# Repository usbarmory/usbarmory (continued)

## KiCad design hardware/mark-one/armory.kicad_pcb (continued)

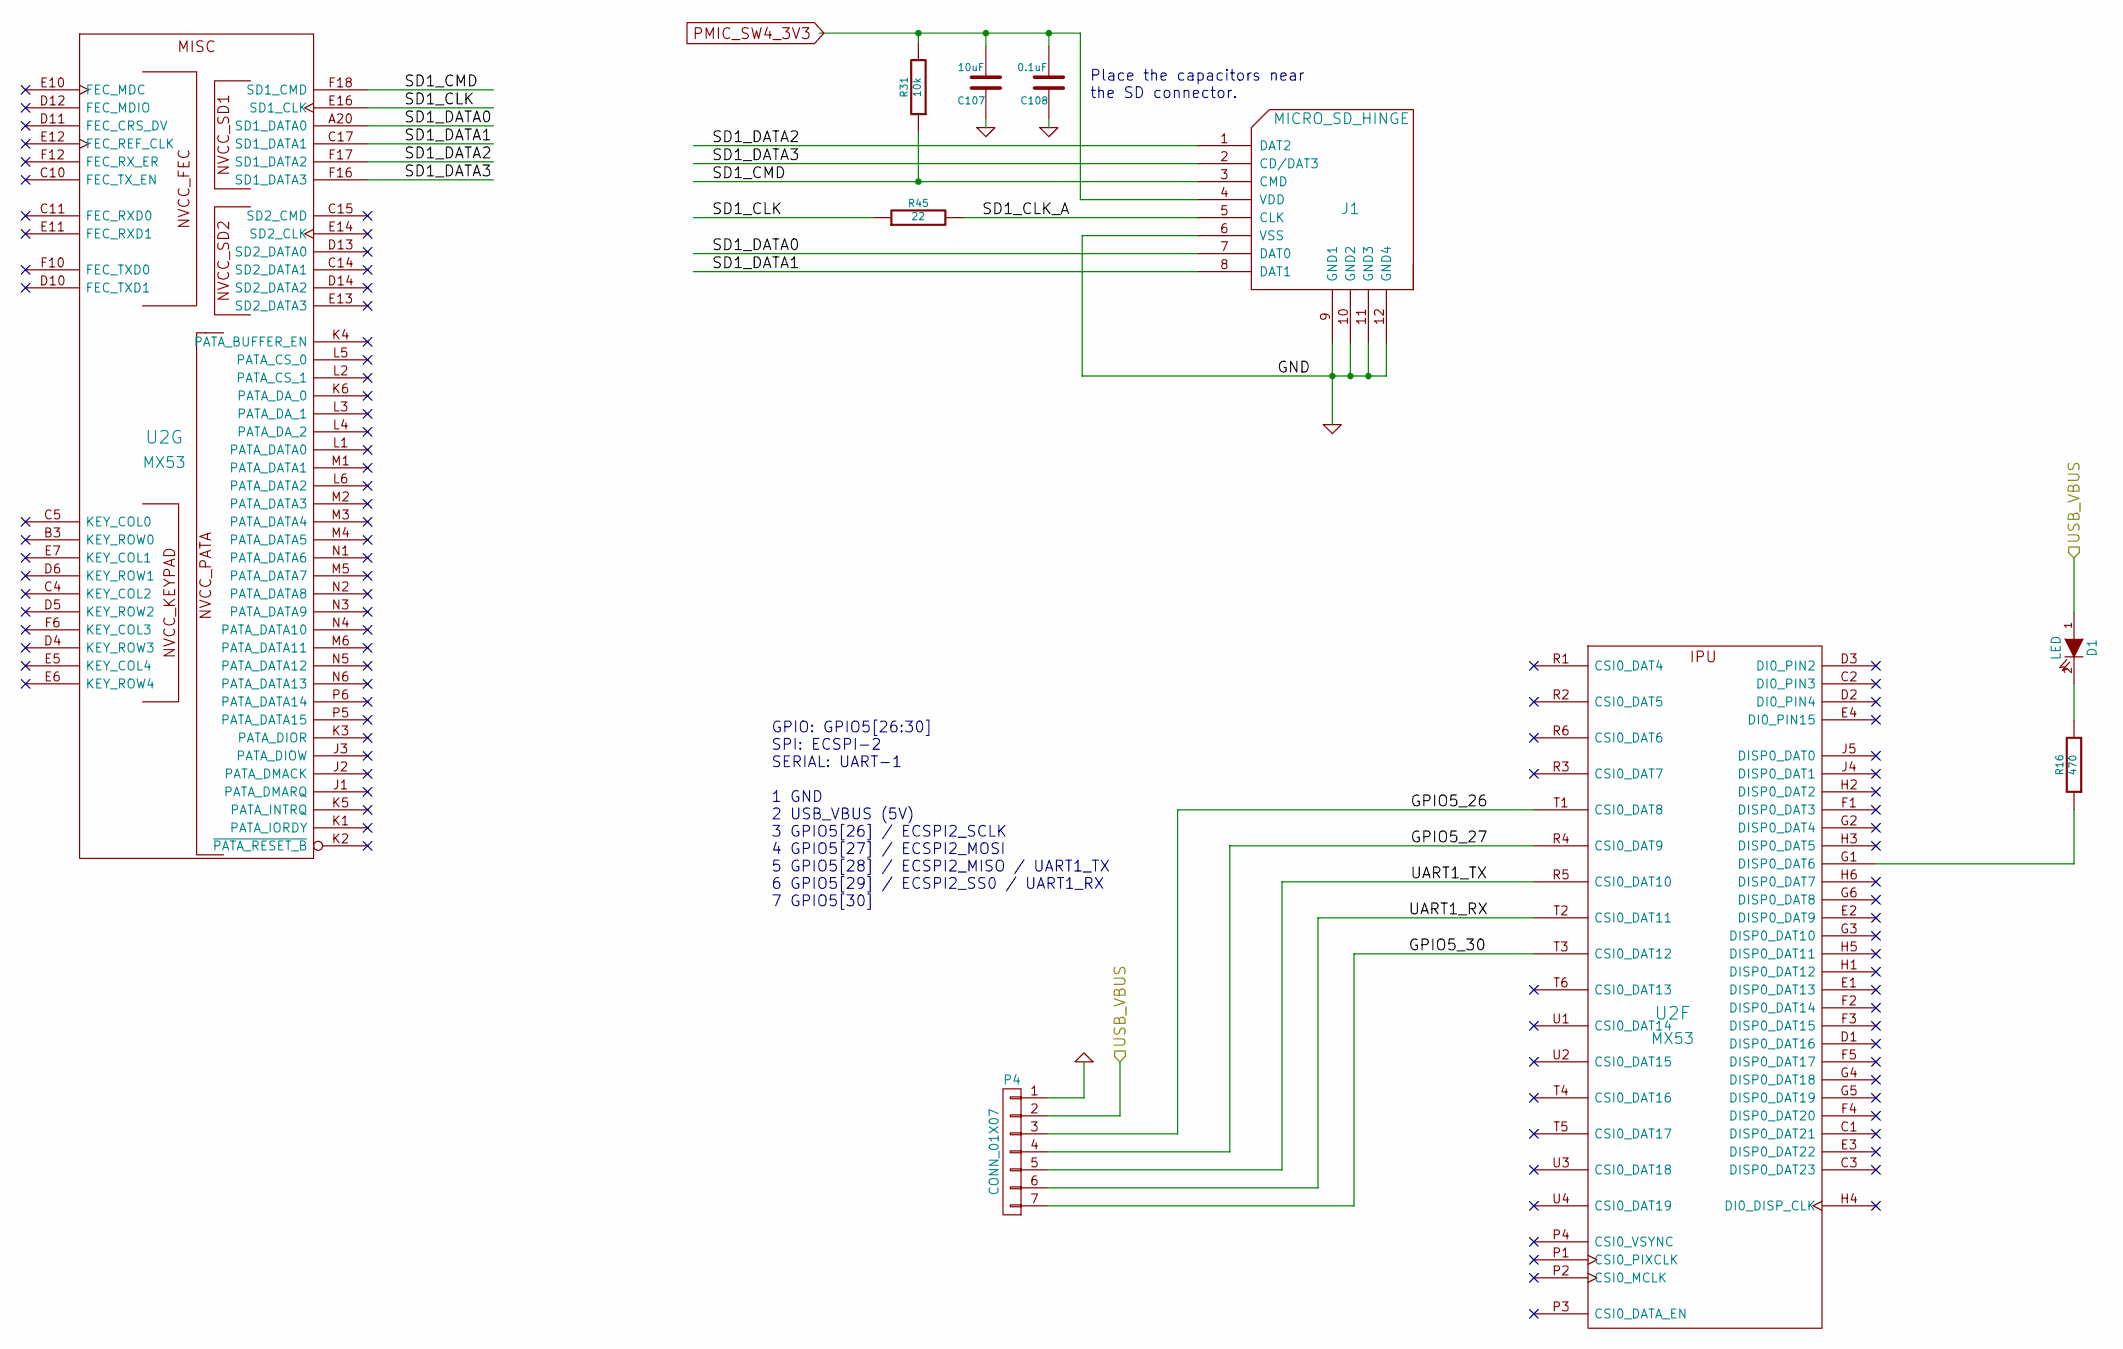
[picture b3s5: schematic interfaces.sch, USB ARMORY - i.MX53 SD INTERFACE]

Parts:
C107: 10uF; SM0603; Mfg PN C1608X5R1A106K080AC
C108: 0.1uF; SM0201; Mfg PN C0603X5R0J104K030BC
D1: LED; SM0603LED; Mfg PN VLMW1300-GS08
J1: MICRO_SD_HINGE; MICRO_SD_HINGE_AMP; Mfg PN 101-00303-68
P4: CONN_01X07; pinhead-1X7
R16: 470; SM0201; Mfg PN CRCW0201470RFNED
R31: 10k; SM0201; Mfg PN CRCW020110K0FNED
R45: 22; SM0201; Mfg PN CRCW020122R0FNED
U2: MX53

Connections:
/Interfaces/GPIO5_26: P4.3, U2.T1 (CSI0_DAT8)
/Interfaces/GPIO5_27: P4.4, U2.R4 (CSI0_DAT9)
/Interfaces/GPIO5_30: P4.7, U2.T3 (CSI0_DAT12)
/Interfaces/SD1_CLK: R45.1, U2.E16 (SD1_CLK)
/Interfaces/SD1_CLK_A: J1.5 (CLK), R45.2
/Interfaces/SD1_CMD: J1.3 (CMD), R31.1, U2.F18 (SD1_CMD)
/Interfaces/SD1_DATA0: J1.7 (DAT0), U2.A20 (SD1_DATA0)
/Interfaces/SD1_DATA1: J1.8 (DAT1), U2.C17 (SD1_DATA1)
/Interfaces/SD1_DATA2: J1.1 (DAT2), U2.F17 (SD1_DATA2)
/Interfaces/SD1_DATA3: J1.2 (CD/DAT3), U2.F16 (SD1_DATA3)
/Interfaces/UART1_RX: P4.6, U2.T2 (CSI0_DAT11)
/Interfaces/UART1_TX: P4.5, U2.R5 (CSI0_DAT10)
/Interfaces/USB_VBUS: D1.1 (A), P4.2; also elsewhere on the board
GND: C107.1, C108.1, J1.6 (VSS), J1.9 (GND1), J1.10 (GND2), J1.11 (GND3), J1.12 (GND4), P4.1; also elsewhere on the board
unnamed: D1.2 (K), R16.2
unnamed: R16.1, U2.G1 (DISP0_DAT6)
PMIC_SW4_3V3: C107.2, C108.2, J1.4 (VDD), R31.2; also elsewhere on the board

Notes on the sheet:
Place the capacitors near the SD connector.
GPIO: GPIO5[26:30] SPI: ECSPI-2 SERIAL: UART-1 1 GND 2 USB_VBUS (5V) 3 GPIO5[26] / ECSPI2_SCLK 4 GPIO5[27] / ECSPI2_MOSI 5 GPIO5[28] / ECSPI2_MISO / UART1_TX 6 GPIO5[29] / ECSPI2_SS0 / UART1_RX 7 GPIO5[30]

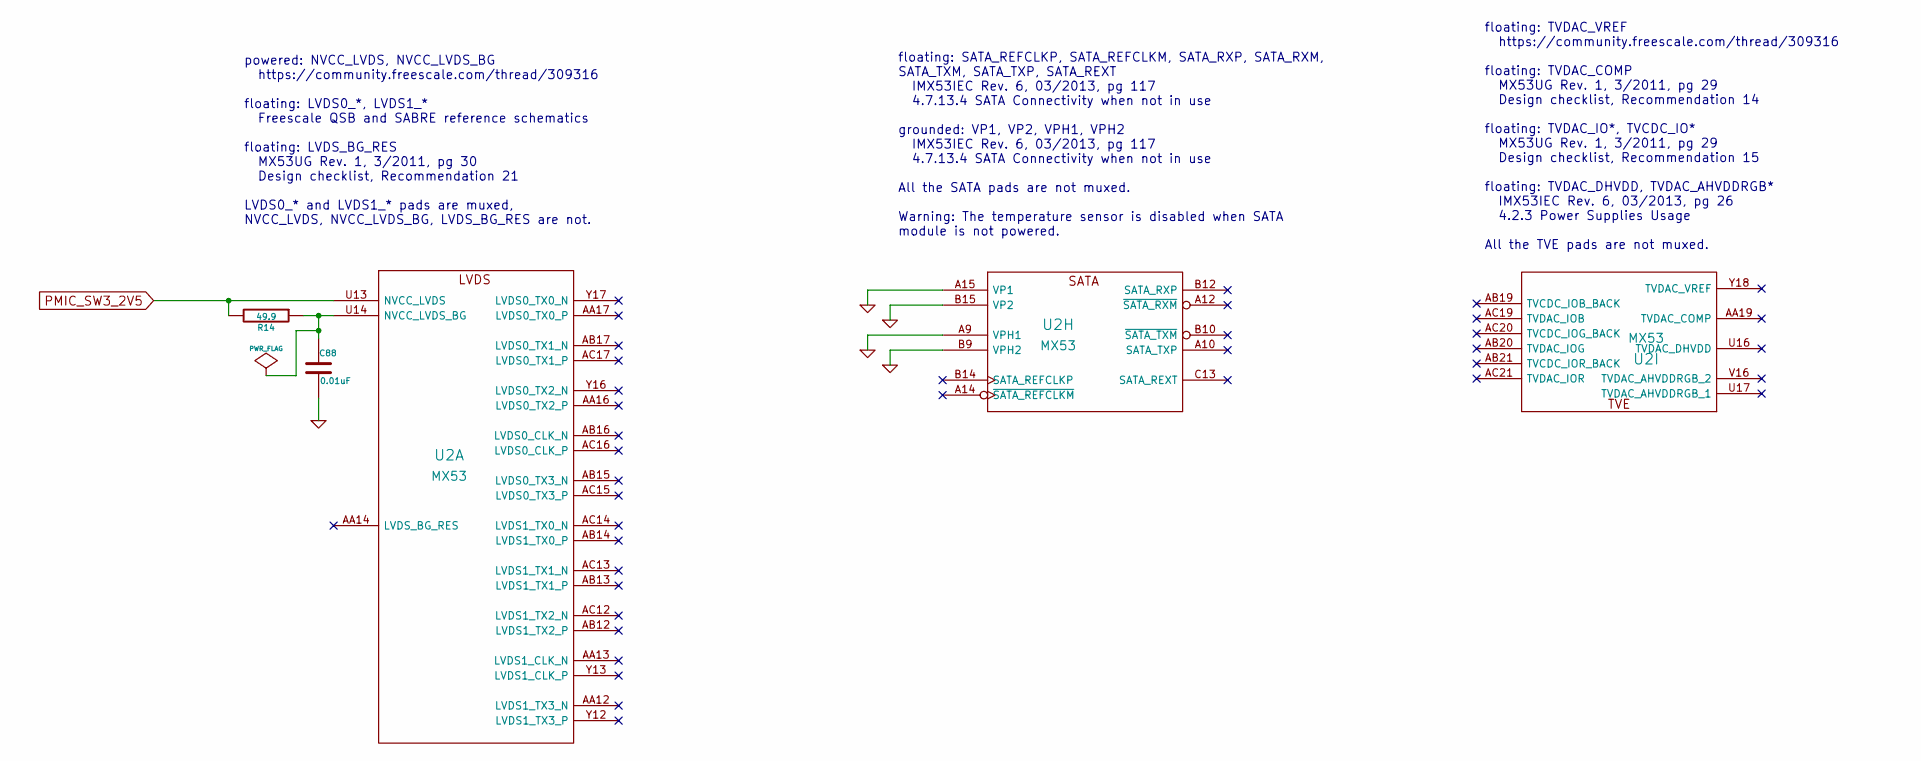
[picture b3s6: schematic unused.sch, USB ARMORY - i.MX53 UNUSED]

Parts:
C88: 0.01uF; SM0201; Mfg PN C0603X7R1A103K030BA
R14: 49.9; SM0201; Mfg PN CRCW020149R9FNED
U2: MX53

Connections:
GND: C88.2, U2.A9 (VPH1), U2.A15 (VP1), U2.B9 (VPH2), U2.B15 (VP2); also elsewhere on the board
unnamed: C88.1, R14.1, U2.U14 (NVCC_LVDS_BG)
PMIC_SW3_2V5: R14.2, U2.U13 (NVCC_LVDS); also elsewhere on the board

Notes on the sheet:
floating: TVDAC_VREF https://community.freescale.com/thread/309316 floating: TVDAC_COMP MX53UG Rev. 1, 3/2011, pg 29 Design checklist, Recommendation 14 floating: TVDAC_IO*, TVCDC_IO* MX53UG Rev. 1, 3/2011, pg 29 Design checklist, Recommendation 15 floating: TVDAC_DHVDD, TVDAC_AHVDDRGB* IMX53IEC Re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
powered: NVCC_LVDS, NVCC_LVDS_BG https://community.freescale.com/thread/309316 floating: LVDS0_*, LVDS1_* Freescale QSB and SABRE reference schematics floating: LVDS_BG_RES MX53UG Rev. 1, 3/2011, pg 30 Design checklist, Recommendation 21 LVDS0_* and LVDS1_* pads are muxed, NVCC_LVDS, NVCC_LVDS_BG, 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
floating: SATA_REFCLKP, SATA_REFCLKM, SATA_RXP, SATA_RXM, SATA_TXM, SATA_TXP, SATA_REXT IMX53IEC Rev. 6, 03/2013, pg 117 4.7.13.4 SATA Connectivity when not in use grounded: VP1, VP2, VPH1, VPH2 IMX53IEC Rev. 6, 03/2013, pg 117 4.7.13.4 SATA Connectivity when not in use All the SATA pads are not mu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

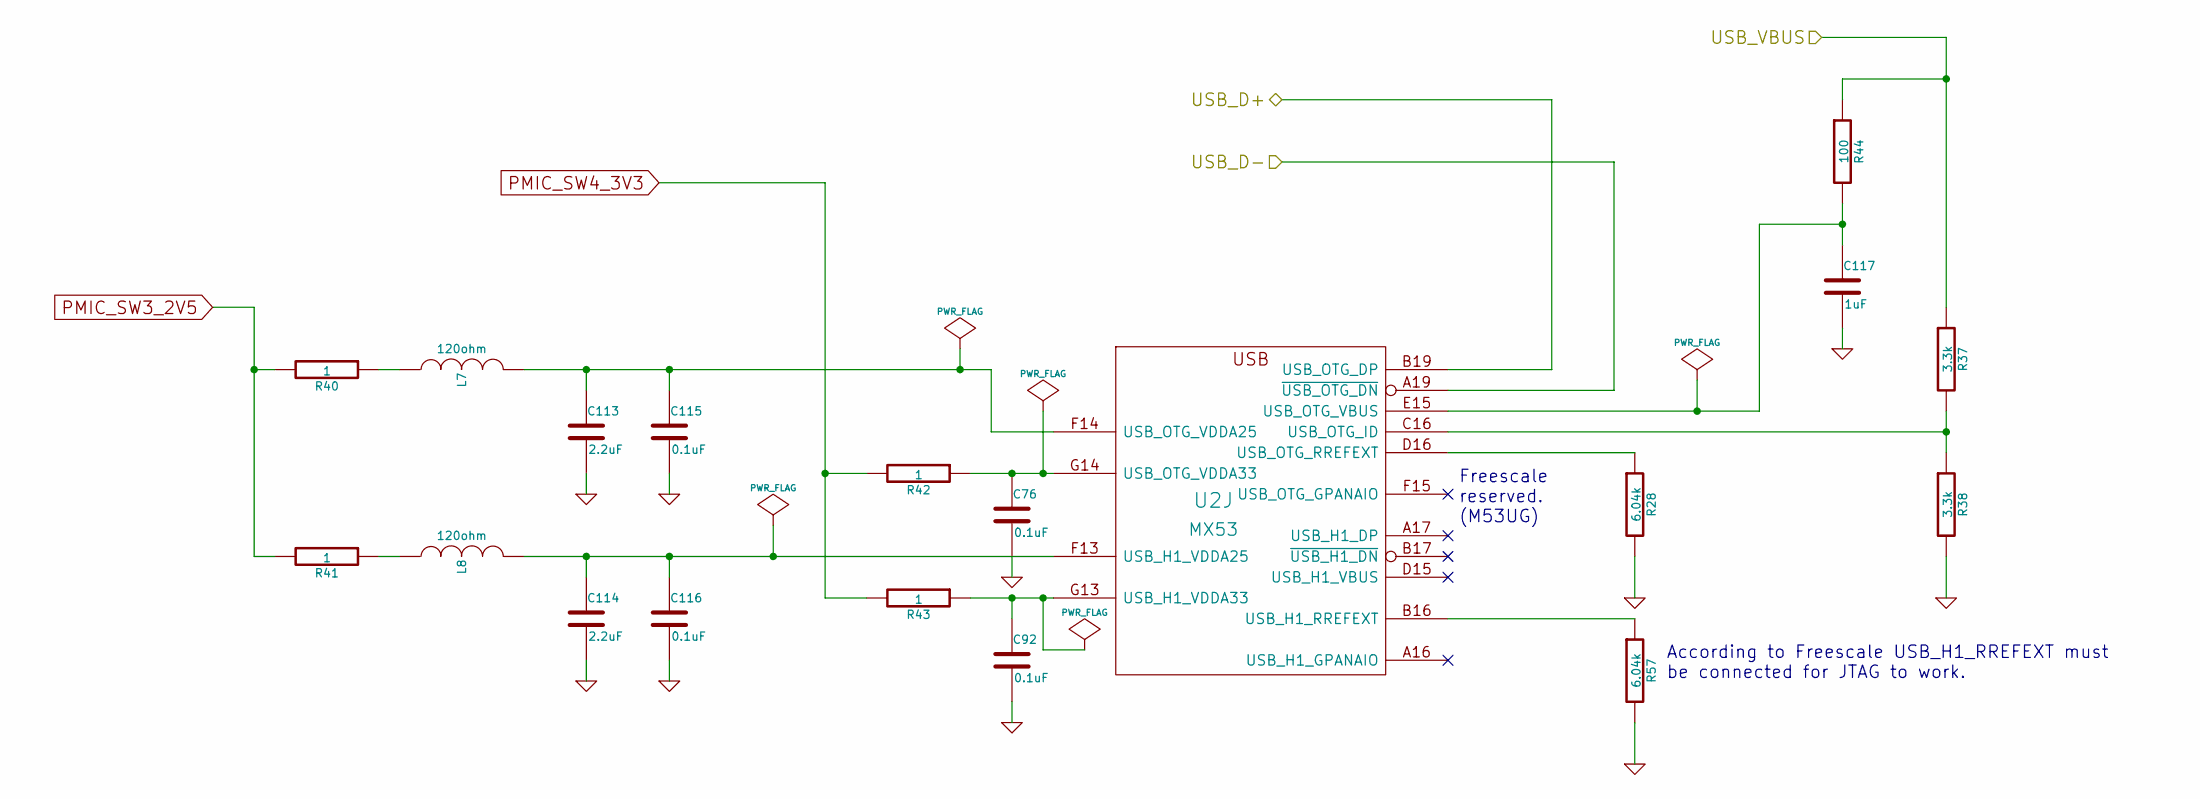
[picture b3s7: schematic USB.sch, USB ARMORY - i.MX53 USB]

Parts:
C76, C92, C115, C116: 0.1uF; SM0201; Mfg PN C0603X5R0J104K030BC
C113, C114: 2.2uF; SM0402; Mfg PN C1005X5R0J225K050BC
C117: 1uF; SM0201; Mfg PN C0603X5R0J105M030BC
L7, L8: 120ohm; SM0201; Mfg PN 742692003
R28, R57: 6.04k; SM0201; Mfg PN CRCW02016K04FNED
R37, R38: 3.3k; SM0201; Mfg PN CRCW02013K30FNED
R40, R41, R42, R43: 1; SM0201; Mfg PN MCRE000220
R44: 100; SM0201; Mfg PN CRCW0201100RFNED
U2: MX53

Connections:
/Interfaces/USB_VBUS: R37.1, R44.1; also elsewhere on the board
/USB/USB_D+: U2.B19 (USB_OTG_DP); also elsewhere on the board
/USB/USB_D-: U2.A19 (~USB_OTG_DN); also elsewhere on the board
GND: C76.2, C92.2, C113.2, C114.2, C115.2, C116.2, C117.2, R28.2, R38.2, R57.2; also elsewhere on the board
unnamed: C76.1, R42.1, U2.G14 (USB_OTG_VDDA33)
unnamed: C92.1, R43.1, U2.G13 (USB_H1_VDDA33)
unnamed: C113.1, C115.1, L7.2, U2.F14 (USB_OTG_VDDA25)
unnamed: C114.1, C116.1, L8.2, U2.F13 (USB_H1_VDDA25)
unnamed: C117.1, R44.2, U2.E15 (USB_OTG_VBUS)
unnamed: L7.1, R40.1
unnamed: L8.1, R41.1
unnamed: R28.1, U2.D16 (USB_OTG_RREFEXT)
unnamed: R37.2, R38.1, U2.C16 (USB_OTG_ID)
unnamed: R57.1, U2.B16 (USB_H1_RREFEXT)
PMIC_SW3_2V5: R40.2, R41.2; also elsewhere on the board
PMIC_SW4_3V3: R42.2, R43.2; also elsewhere on the board

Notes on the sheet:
Freescale reserved. (M53UG)
According to Freescale USB_H1_RREFEXT must be connected for JTAG to work.

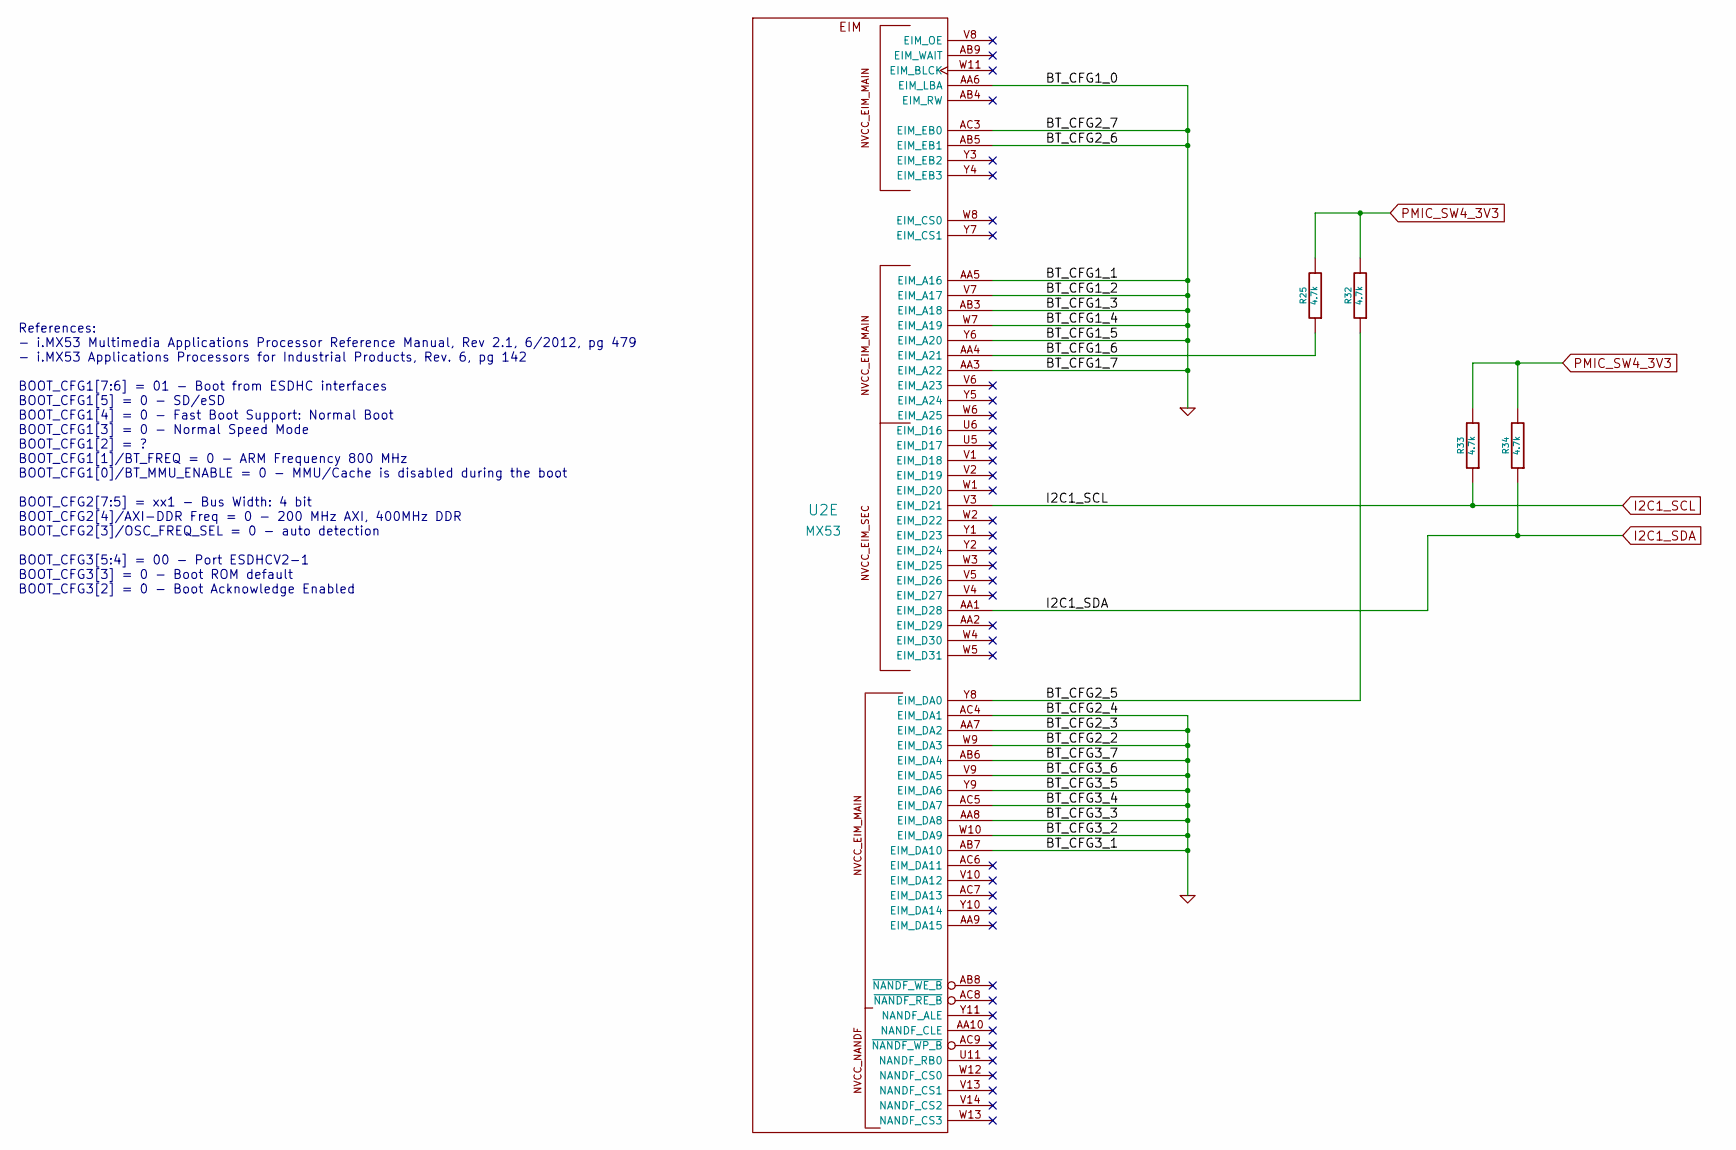
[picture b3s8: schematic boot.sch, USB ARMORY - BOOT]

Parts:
R25, R32, R33, R34: 4.7k; SM0201; Mfg PN CRCW02014K70FNED
U2: MX53

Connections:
/Boot/BT_CFG1_6: R25.1, U2.AA4 (EIM_A21)
/Boot/BT_CFG2_5: R32.1, U2.Y8 (EIM_DA0)
GND: U2.AA3 (EIM_A22), U2.AA5 (EIM_A16), U2.AA6 (EIM_LBA), U2.AA7 (EIM_DA2), U2.AA8 (EIM_DA8), U2.AB3 (EIM_A18), U2.AB5 (EIM_EB1), U2.AB6 (EIM_DA4), U2.AB7 (EIM_DA10), U2.AC3 (EIM_EB0), U2.AC4 (EIM_DA1), U2.AC5 (EIM_DA7), U2.V7 (EIM_A17), U2.V9 (EIM_DA5), U2.W7 (EIM_A19), U2.W9 (EIM_DA3), U2.W10 (EIM_DA9), U2.Y6 (EIM_A20), U2.Y9 (EIM_DA6); also elsewhere on the board
I2C1_SCL: R33.1, U2.V3 (EIM_D21); also elsewhere on the board
I2C1_SDA: R34.1, U2.AA1 (EIM_D28); also elsewhere on the board
PMIC_SW4_3V3: R25.2, R32.2, R33.2, R34.2; also elsewhere on the board

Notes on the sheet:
References: - i.MX53 Multimedia Applications Processor Reference Manual, Rev 2.1, 6/2012, pg 479 - i.MX53 Applications Processors for Industrial Products, Rev. 6, pg 142 BOOT_CFG1[7:6] = 01 - Boot from ESDHC interfaces BOOT_CFG1[5] = 0 - SD/eSD BOOT_CFG1[4] = 0 - Fast Boot Support: Normal Boot BOOT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

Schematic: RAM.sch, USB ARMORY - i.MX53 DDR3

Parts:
C89, C90, C91, C93, C94, C96, C97, C98, C100, C101, C102, C104: 0.1uF; SM0201; Mfg PN C0603X5R0J104K030BC
C95, C99, C103: 0.01uF; SM0201; Mfg PN C0603X7R1A103K030BA
C105, C106: 10uF; SM0603; Mfg PN C1608X5R1A106K080AC
P3: TST; TP
R15, R24: 470; SM0201; Mfg PN CRCW0201470RFNED
R27, R29: 240; SM0201; Mfg PN CRCW0201240RFNED
R30: 100; SM0603; Mfg PN CRCW0603100RFKEA
U2: MX53
U4: MT41K256M16HA; micron-96-fbga-ha; Mfg PN MT41K256M16HA-107

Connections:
/RAM/DDR_VREF: C89.1, C90.2, C91.1, C93.1, P3.1, R15.1, R24.2, U2.L17 (DDR_VREF), U4.H1 (VREFDQ), U4.M8 (VREFCA)
/RAM/DDR_ZQ: R29.2, U4.L8 (ZQ)
/RAM/DRAM_A0: U2.M19 (DRAM_A0), U4.N3 (A0)
/RAM/DRAM_A1: U2.L21 (DRAM_A1), U4.P7 (A1)
/RAM/DRAM_A2: U2.M20 (DRAM_A2), U4.P3 (A2)
/RAM/DRAM_A3: U2.N20 (DRAM_A3), U4.N2 (A3)
/RAM/DRAM_A4: U2.K20 (DRAM_A4), U4.P8 (A4)
/RAM/DRAM_A5: U2.N21 (DRAM_A5), U4.P2 (A5)
/RAM/DRAM_A6: U2.M22 (DRAM_A6), U4.R8 (A6)
/RAM/DRAM_A7: U2.N22 (DRAM_A7), U4.R2 (A7)
/RAM/DRAM_A8: U2.N23 (DRAM_A8), U4.T8 (A8)
/RAM/DRAM_A9: U2.M21 (DRAM_A9), U4.R3 (A9)
/RAM/DRAM_A10: U2.K19 (DRAM_A10), U4.L7 (A10/AP)
/RAM/DRAM_A11: U2.L22 (DRAM_A11), U4.R7 (A11)
/RAM/DRAM_A12: U2.L20 (DRAM_A12), U4.N7 (A12/~BC)
/RAM/DRAM_A13: U2.L23 (DRAM_A13), U4.T3 (A13)
/RAM/DRAM_A14: U2.N18 (DRAM_A14), U4.T7 (A14)
/RAM/DRAM_CALIBRATION: R27.2, U2.M23 (DRAM_CALIBRATION)
/RAM/DRAM_CAS: U2.L18 (DRAM_CAS), U4.K3 (~CAS)
/RAM/DRAM_CS0: U2.K18 (DRAM_CS0), U4.L2 (~CS)
/RAM/DRAM_D0: U2.H20 (DRAM_D0), U4.E3 (DQ0)
/RAM/DRAM_D1: U2.G21 (DRAM_D1), U4.F7 (DQ1)
/RAM/DRAM_D2: U2.J21 (DRAM_D2), U4.F2 (DQ2)
/RAM/DRAM_D3: U2.G20 (DRAM_D3), U4.F8 (DQ3)
/RAM/DRAM_D4: U2.J23 (DRAM_D4), U4.H3 (DQ4)
/RAM/DRAM_D5: U2.G23 (DRAM_D5), U4.H8 (DQ5)
/RAM/DRAM_D6: U2.J22 (DRAM_D6), U4.G2 (DQ6)
/RAM/DRAM_D7: U2.G22 (DRAM_D7), U4.H7 (DQ7)
/RAM/DRAM_D8: U2.E21 (DRAM_D8), U4.D7 (DQ8)
/RAM/DRAM_D9: U2.D21 (DRAM_D9), U4.C3 (DQ9)
/RAM/DRAM_D10: U2.E22 (DRAM_D10), U4.C8 (DQ10)
/RAM/DRAM_D11: U2.D20 (DRAM_D11), U4.C2 (DQ11)
/RAM/DRAM_D12: U2.E23 (DRAM_D12), U4.A7 (DQ12)
/RAM/DRAM_D13: U2.C23 (DRAM_D13), U4.A2 (DQ13)
/RAM/DRAM_D14: U2.F23 (DRAM_D14), U4.B8 (DQ14)
/RAM/DRAM_D15: U2.C22 (DRAM_D15), U4.A3 (DQ15)
/RAM/DRAM_DQM0: U2.H21 (DRAM_DQM0), U4.E7 (LDM)
/RAM/DRAM_DQM1: U2.E20 (DRAM_DQM1), U4.D3 (UDM)
/RAM/DRAM_RAS: U2.J19 (DRAM_RAS), U4.J3 (~RAS)
/RAM/DRAM_RESET: U2.P18 (DRAM_RESET), U4.T2 (~RESET)
/RAM/DRAM_SDBA0: U2.R19 (DRAM_SDBA0), U4.M2 (BA0)
/RAM/DRAM_SDBA1: U2.P20 (DRAM_SDBA1), U4.N8 (BA1)
/RAM/DRAM_SDBA2: U2.N19 (DRAM_SDBA2), U4.M3 (BA2)
/RAM/DRAM_SDCKE0: U2.H19 (DRAM_SDCKE0), U4.K9 (CKE)
/RAM/DRAM_SDCLK_0: R30.1, U2.K23 (DRAM_SDCLK_0), U4.J7 (CK)
/RAM/DRAM_SDCLK_0_B: R30.2, U2.K22 (~DRAM_SDCLK_0_B), U4.K7 (~CK)
/RAM/DRAM_SDODT0: U2.J18 (DRAM_SDODT0), U4.K1 (ODT)
/RAM/DRAM_SDQS0: U2.H23 (DRAM_SDQS0), U4.F3 (LDQS)
/RAM/DRAM_SDQS0_B: U2.H22 (~DRAM_SDQS0_B), U4.G3 (~LDQS)
/RAM/DRAM_SDQS1: U2.D23 (DRAM_SDQS1), U4.C7 (UDQS)
/RAM/DRAM_SDQS1_B: U2.D22 (~DRAM_SDQS1_B), U4.B7 (~UDQS)
/RAM/DRAM_WE: U2.L19 (DRAM_SDWE), U4.L3 (~WE)
GND: C89.2, C91.2, C93.2, C94.2, C95.2, C96.2, C97.2, C98.2, C99.2, C100.2, C101.2, C102.2, C103.2, C104.2, C105.2, C106.2, R24.1, R27.1, R29.1, U4.A9 (VSS1), U4.B1 (VSSQ1), U4.B3 (VSS2), U4.B9 (VSSQ2), U4.D1 (VSSQ3), U4.D8 (VSSQ4), U4.E1 (VSS3), U4.E2 (VSSQ5), U4.E8 (VSSQ6), U4.F9 (VSSQ7), U4.G1 (VSSQ8), U4.G8 (VSS4), U4.G9 (VSSQ9), U4.J2 (VSS5), U4.J8 (VSS6), U4.M9 (VSS8), U4.P1 (VSS9), U4.P9 (VSS10), U4.T1 (VSS11), U4.T9 (VSS12); also elsewhere on the board
PMIC_DDR_1V5: C90.1, C94.1, C95.1, C96.1, C97.1, C98.1, C99.1, C100.1, C101.1, C102.1, C103.1, C104.1, C105.1, C106.1, R15.2, U4.A1 (VDDQ1), U4.A8 (VDDQ2), U4.B2 (VDD1), U4.C1 (VDDQ3), U4.C9 (VDDQ4), U4.D2 (VDDQ5), U4.D9 (VDD2), U4.E9 (VDDQ6), U4.F1 (VDDQ7), U4.G7 (VDD3), U4.H2 (VDDQ8), U4.H9 (VDDQ9), U4.K2 (VDD4), U4.K8 (VDD5), U4.N1 (VDD6), U4.N9 (VDD7), U4.R1 (VDD8), U4.R9 (VDD9); also elsewhere on the board

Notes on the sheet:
Place near the VDD balls.
Place near the VDDQ balls.

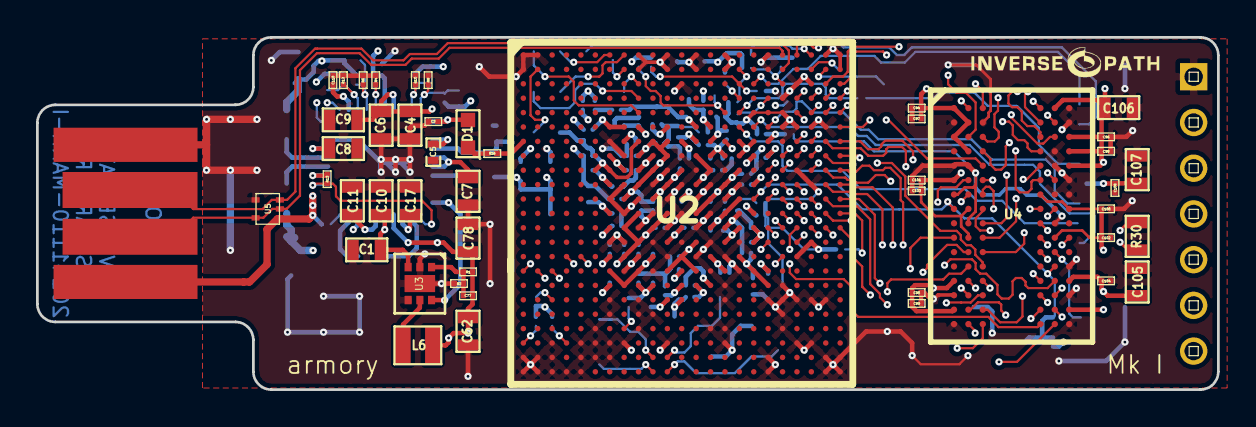
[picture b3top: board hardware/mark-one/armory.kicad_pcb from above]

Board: 8 copper layers, 65.6 x 19.6 mm, 186 parts (0 on the bottom side), 126 nets.

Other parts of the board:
Ref**: Val**; LOGO_SMALL

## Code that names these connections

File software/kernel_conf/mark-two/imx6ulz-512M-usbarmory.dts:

/*
 * USB armory Mk II device tree file
 * https://github.com/inversepath/usbarmory
 *
 * Copyright (c) The USB armory authors
 * Andrej Rosano <andrej@inversepath.com>
 *
 * This file is dual-licensed: you can use it either under the terms
 * of the GPL or the X11 license, at your option. Note that this dual
 * licensing only applies to this file, and not this project as a
 * whole.
 *
 *  a) This file is free software; you can redistribute it and/or
 *     modify it under the terms of the GNU General Public License as
 *     published by the Free Software Foundation; either version 2 of the
 *     License, or (at your option) any later version.
 *
 *     This file is distributed in the hope that it will be useful,
 *     but WITHOUT ANY WARRANTY; without even the implied warranty of
 *     MERCHANTABILITY or FITNESS FOR A PARTICULAR PURPOSE.  See the
 *     GNU General Public License for more details.
 *
 * Or, alternatively,
 *
 *  b) Permission is hereby granted, free of charge, to any person
 *     obtaining a copy of this software and associated documentation
 *     files (the "Software"), to deal in the Software without
 *     restriction, including without limitation the rights to use,
 *     copy, modify, merge, publish, distribute, sublicense, and/or
 *     sell copies of the Software, and to permit persons to whom the
 *     Software is furnished to do so, subject to the following
 *     conditions:
 *
 *     The above copyright notice and this permission notice shall be
 *     included in all copies or substantial portions of the Software.
 *
 *     THE SOFTWARE IS PROVIDED "AS IS", WITHOUT WARRANTY OF ANY KIND,
 *     EXPRESS OR IMPLIED, INCLUDING BUT NOT LIMITED TO THE WARRANTIES
 *     OF MERCHANTABILITY, FITNESS FOR A PARTICULAR PURPOSE AND
 *     NONINFRINGEMENT. IN NO EVENT SHALL THE AUTHORS OR COPYRIGHT
 *     HOLDERS BE LIABLE FOR ANY CLAIM, DAMAGES OR OTHER LIABILITY,
 *     WHETHER IN AN ACTION OF CONTRACT, TORT OR OTHERWISE, ARISING
 *     FROM, OUT OF OR IN CONNECTION WITH THE SOFTWARE OR THE USE OR
 *     OTHER DEALINGS IN THE SOFTWARE.
 */

/dts-v1/;

#include "imx6ulz.dtsi"

/ {
	model = "F-Secure USB armory Mk II";
	compatible = "inversepath,imx6ulz-usbarmory-mkII", "fsl,imx6ull";

	chosen {
		stdout-path = &uart2;
	};

	memory {
		device_type = "memory";
		reg = <0x80000000 0x20000000>;
	};

	leds {
		compatible = "gpio-leds";
		pinctrl-names = "default";
		pinctrl-0 = <&pinctrl_led>;

		led-white {
			label = "LED_WHITE";
			gpios = <&gpio4 21 GPIO_ACTIVE_LOW>;
			linux,default-trigger = "heartbeat";
		};

		led-blue {
			label = "LED_BLUE";
			gpios = <&gpio4 22 GPIO_ACTIVE_LOW>;
		};
	};

	regulators {
		compatible = "simple-bus";
		#address-cells = <1>;
		#size-cells = <0>;

		reg_sd1_vmmc: sd1_regulator {
			compatible = "regulator-fixed";
			regulator-name = "VSD_3V3";
			regulator-min-microvolt = <3300000>;
			regulator-max-microvolt = <3300000>;
		};
	};
};

&uart1 {
	pinctrl-names = "default";
	pinctrl-0 = <&pinctrl_bluetooth>;
	status = "okay";
};

&uart2 {
	pinctrl-names = "default";
	pinctrl-0 = <&pinctrl_uart2>;
	status = "okay";
};

&usdhc1 {
	pinctrl-names = "default";
	pinctrl-0 = <&pinctrl_usdhc1>;
	no-1-8-v;
	keep-power-in-suspend;
	wakeup-source;
	status = "okay";
};

&usdhc2 {
	pinctrl-names = "default", "state_100mhz", "state_200mhz";
	pinctrl-0 = <&pinctrl_usdhc2>;
	pinctrl-1 = <&pinctrl_usdhc2_100mhz>;
	pinctrl-2 = <&pinctrl_usdhc2_200mhz>;
	bus-width = <8>;
	non-removable;
	status = "okay";
};

&i2c1 {
	pinctrl-0 = <&pinctrl_i2c1>;
	status = "okay";
};

&ecspi1 {
	pinctrl-names = "default";
	pinctrl-0 = <&pinctrl_ecspi1>;
	status = "okay";

	spidev0: spi@0 {
		compatible = "rohm,dh2228fv";
		reg = <0>;
		spi-max-frequency = <5000000>;
	};
};

&iomuxc {
	pinctrl_uart2: uart2grp {
		fsl,pins = <
			MX6UL_PAD_UART2_TX_DATA__UART2_DCE_TX	0x1b0b1
			MX6UL_PAD_UART2_RX_DATA__UART2_DCE_RX	0x1b0b1
		>;
	};

	pinctrl_bluetooth: uart1grp {
		fsl,pins = <
			MX6UL_PAD_UART1_TX_DATA__UART1_DCE_TX	0x1b0b0 /* BT_UART_TX  */
			MX6UL_PAD_UART1_RX_DATA__UART1_DCE_RX	0x1b0b0 /* BT_UART_RX  */
			MX6UL_PAD_UART1_CTS_B__UART1_DCE_CTS	0x1b0b0 /* BT_UART_CTS */
			MX6UL_PAD_GPIO1_IO07__UART1_DCE_RTS	0x130b0 /* BT_UART_RTS */
			MX6UL_PAD_UART3_TX_DATA__GPIO1_IO24	0x1f020 /* BT_UART_DSR */
			MX6UL_PAD_UART3_RX_DATA__GPIO1_IO25	0x10020 /* BT_UART_DTR */
			MX6UL_PAD_GPIO1_IO04__GPIO1_IO04	0x1f020 /* BT_SWDCLK   */
			MX6UL_PAD_GPIO1_IO06__GPIO1_IO06	0x1f020 /* BT_SWDIO    */
			MX6UL_PAD_GPIO1_IO09__GPIO1_IO09	0x1f020 /* BT_RESET    */
			MX6UL_PAD_UART3_RTS_B__GPIO1_IO27	0x1f020 /* BT_SWITCH_1 */
			MX6UL_PAD_UART3_CTS_B__GPIO1_IO26	0x1f020 /* BT_SWITCH_2 */
		>;
	};

	pinctrl_i2c1: i2c1grp {
		fsl,pins = <
			MX6UL_PAD_GPIO1_IO02__I2C1_SCL	0x4001b8b0
			MX6UL_PAD_GPIO1_IO03__I2C1_SDA	0x4001b8b0
		>;
	};

	pinctrl_ecspi1: ecspi1grp {
		fsl,pins = <
			MX6UL_PAD_LCD_DATA19__GPIO3_IO24	0x0b0b0 /* TROPIC_GP */
			MX6UL_PAD_LCD_DATA20__ECSPI1_SCLK	0x0b0b0 /* CSPI_SCLK */
			MX6UL_PAD_LCD_DATA21__GPIO3_IO26	0x0b0b0 /* CSPI_SS */
			MX6UL_PAD_LCD_DATA22__ECSPI1_MOSI	0x0b0b0 /* CSPI_MOSI */
			MX6UL_PAD_LCD_DATA23__ECSPI1_MISO	0x0b0b0 /* CSPI_MISO */
		>;
	};

	pinctrl_led: ledgrp {
		fsl,pins = <
			MX6UL_PAD_CSI_DATA00__GPIO4_IO21	0x1f020
			MX6UL_PAD_CSI_DATA01__GPIO4_IO22	0x1f020
		>;
	};

	pinctrl_usdhc1: usdhc1grp {
		fsl,pins = <
			MX6UL_PAD_SD1_CMD__USDHC1_CMD		0x1f019
			MX6UL_PAD_SD1_CLK__USDHC1_CLK		0x1f019
			MX6UL_PAD_SD1_DATA0__USDHC1_DATA0	0x1f019
			MX6UL_PAD_SD1_DATA1__USDHC1_DATA1	0x1f019
			MX6UL_PAD_SD1_DATA2__USDHC1_DATA2	0x1f019
			MX6UL_PAD_SD1_DATA3__USDHC1_DATA3	0x1f019
		>;
	};

	pinctrl_usdhc2: usdhc2grp {
		fsl,pins = <
			MX6UL_PAD_NAND_RE_B__USDHC2_CLK		0x10069
			MX6UL_PAD_NAND_WE_B__USDHC2_CMD		0x17059
			MX6UL_PAD_NAND_DATA00__USDHC2_DATA0	0x17059
			MX6UL_PAD_NAND_DATA01__USDHC2_DATA1	0x17059
			MX6UL_PAD_NAND_DATA02__USDHC2_DATA2	0x17059
			MX6UL_PAD_NAND_DATA03__USDHC2_DATA3	0x17059
			MX6UL_PAD_NAND_DATA04__USDHC2_DATA4	0x17059
			MX6UL_PAD_NAND_DATA05__USDHC2_DATA5	0x17059
			MX6UL_PAD_NAND_DATA06__USDHC2_DATA6	0x17059
			MX6UL_PAD_NAND_DATA07__USDHC2_DATA7	0x17059
		>;
	};

	pinctrl_usdhc2_100mhz: usdhc2grp_100mhz {
		fsl,pins = <
			MX6UL_PAD_NAND_RE_B__USDHC2_CLK		0x100b9
			MX6UL_PAD_NAND_WE_B__USDHC2_CMD		0x170b9
			MX6UL_PAD_NAND_DATA00__USDHC2_DATA0	0x170b9
			MX6UL_PAD_NAND_DATA01__USDHC2_DATA1	0x170b9
			MX6UL_PAD_NAND_DATA02__USDHC2_DATA2	0x170b9
			MX6UL_PAD_NAND_DATA03__USDHC2_DATA3	0x170b9
			MX6UL_PAD_NAND_DATA04__USDHC2_DATA4	0x170b9
			MX6UL_PAD_NAND_DATA05__USDHC2_DATA5	0x170b9
			MX6UL_PAD_NAND_DATA06__USDHC2_DATA6	0x170b9
			MX6UL_PAD_NAND_DATA07__USDHC2_DATA7	0x170b9
		>;
	};

	pinctrl_usdhc2_200mhz: usdhc2grp_200mhz {
		fsl,pins = <
			MX6UL_PAD_NAND_RE_B__USDHC2_CLK		0x100f9
			MX6UL_PAD_NAND_WE_B__USDHC2_CMD		0x170f9
			MX6UL_PAD_NAND_DATA00__USDHC2_DATA0	0x170f9
			MX6UL_PAD_NAND_DATA01__USDHC2_DATA1	0x170f9
			MX6UL_PAD_NAND_DATA02__USDHC2_DATA2	0x170f9
			MX6UL_PAD_NAND_DATA03__USDHC2_DATA3	0x170f9
			MX6UL_PAD_NAND_DATA04__USDHC2_DATA4	0x170f9
			MX6UL_PAD_NAND_DATA05__USDHC2_DATA5	0x170f9
			MX6UL_PAD_NAND_DATA06__USDHC2_DATA6	0x170f9
			MX6UL_PAD_NAND_DATA07__USDHC2_DATA7	0x170f9
		>;
	};
};

&usbotg1 {
	dr_mode = "peripheral";
	disable-over-current;
	tpl-support;
	status = "okay";
};

&usbotg2 {
	dr_mode = "host";
	disable-over-current;
	tpl-support;
	status = "okay";
};

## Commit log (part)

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2016-06-08 Remove old U-Boot patches
2016-06-09 bump buildroot INTERLOCK revision
2016-06-20 Add patch for disabling U-Boot CLI
2016-06-21 devicetree: explicitly set IOMUX values
    Do not relay on bootloader values (e.g. using 0x80000000 settings).
2016-06-21 devicetree: remove vpu node
    VPU is already enabled in imx53.dtsi.
2016-06-23 out of an abundance of caution (as at that time haveged already took care of the pool) ensure that there is enough entropy for luksFormat command
2016-06-28 Update kernel config
    Add stack protector and DMA contiguous access support.
2016-06-29 add SCCv2 device
2016-07-01 add mxc-scc2 driver in buildroot image and fix invalid date reset format
2016-07-03 tidying
2016-07-27 Update kernel config
    Use regular stack protection as gcc included in some main Linux
    distributions does not support -fstack-protector-strong flag yet.
2016-08-31 Add config for Linux 4.7
2016-09-16 isolate networking and INTERLOCK overlays for better modularity and bump revisions
2016-09-19 buildroot overlays/profiles re-org
2016-10-12 csftool: add support for Serial download mode when using DCD
    When DCD is used, Serial downloader will move DCD into ocram and clear
    the DCD pointer in IVT - before signature verification.
    To sign the image properly we need to:
    - clear the DCD pointer in IVT and calculate signature on this modified image
    - make a signature for DCD copy in ocram (usually from 0x910000)
2016-10-12 typo fix
2016-10-12 disable NTP server to favor manual configuration by user
2016-10-12 set static CDC Ethernet MAC address
2016-10-12 buildroot fixes: ensure LED is turned on last at shutdown, tidy overlay structure
2016-10-14 Add config for Linux 4.8
2016-10-21 bugfixes for qubes-gpg-split/gpg-server execution
2016-10-31 bump buildroot INTERLOCK and kernel revision
2016-11-08 improve readibility
2016-11-08 Fix typo
2016-11-09 check for dropbearkey dependency and note it in documentation
2016-11-10 fail on any post build error
2016-11-14 style consistency fixes
2016-11-15 lock alias now actually locks the partition
2016-11-15 add missing sudo
2016-11-16 bump kernel
2016-11-16 set default LED timeout if not specified
2016-11-17 Updated kernel configuration.
    Add support for EXT4 extended attributes to allow setcap, enable /proc/config.gz by default.
2016-11-22 replace diagram
2016-12-13 Clean old kernel configs
2016-12-13 Update devicetree files
    Add dts files for kernel 4.9. Move old dts files to dts-4.8 directory.
2016-12-15 restore scc2 dts entry in separate file
2017-01-14 PaX/Grsecurity 4.8 for USBArmory
2017-01-14 More exploit mitigation on Linux v4.9
2017-02-15 PaX/Grsecurity 4.9 for USBArmory:
    PaX/Grsecurity 4.9 with BBR enabled for the case of tor-router usage.
2017-02-15 PaX/Grsecurity 4.9 for USBArmory: (#38)
    PaX/Grsecurity 4.9 with BBR enabled for the case of tor-router usage.
2017-03-07 bump buildroot, INTERLOCK and mxc-scc2 revisions
2017-03-15 cryptsetup aes-xts-plain64 is broken under 4.10 kernel when sahara is enabled, make it a module for blacklisting when required
2017-05-24 bump buildroot and kernel revision
2017-06-05 add preliminary HAB security advisory
2017-07-19 CVE-2017-7932 PoC and advisory update
2017-07-27 added link to i.MX Community post that lists affected P/Ns
2017-08-07 bump INTERLOCK version
2017-11-17 update kernel conf
2018-01-08 update buildroot environment
2018-01-09 adjust mkfs.ext4 path due to change in newer buildroot
2018-01-15 Enable kernel namespaces
2018-02-13 Fix ext2load dependancy in secure boot patches
2018-02-14 bump initial system date
2018-02-15 Enable hab_status in secure boot patches
2018-02-20 Add linux kernel 4.14 config
2018-02-26 Fix disable CLI patch
    2018.01 U-Boot requires CONFIG_USE_BOOTARGS
2018-02-28 bump buildroot kernel, U-Boot and INTERLOCK versions
2018-05-08 Fix ext2load command not available error
2018-07-10 copyright change
2018-10-18 tidying
    Remove configurations for unmantained kernel versions
2018-11-01 Add devicetree with CAAM for i.MX6UL PICO board
2018-11-01 Add buildroot caam-keyblob package
2018-11-01 Bump U-Boot in INTERLOCK buildroot for i.MX6UL PICO
2018-11-01 Tyding
2018-11-01 Add i.MX6UL PICO secure boot support
2018-11-02 U-Boot security advisory (CVE-2018-18440, CVE-2018-18439)
2018-11-02 Remove unnecessary U-Boot environment variables
2018-11-02 imx6ul-pico: add patch for disabling U-Boot CLI
2018-11-27 adjust buildroot profiles to use intree dts
2018-12-04 fix documentation - dtb destination file
2018-12-18 bump caam-keyblob version
2019-02-01 maintain original dtb name to respect usbarmory.its path
2019-02-01 Update buildroot release and kernel version
2019-03-19 Fix i2c, spi and gpio devicetree
    iomux pinctrl configuration should be placed in module structure instead
    of the 'iomux' one. This behaviour seems to have changed in recent
    kernels.
2019-03-20 Fix I2C, GPIO and SPI devicetree files
    Remove container node from iomuxc nodes.
2019-03-28 bump buildroot and kernel versions for INTERLOCK profile
2019-04-01 move mark-one specific design files in own directory
2019-04-03 Set SION bit for i2c pads
2019-04-10 i.MX6UL* bootrom dump utility
2019-05-06 Update 4.14 kernel config
2019-05-06 enable local system does not support BPF/cgroup based firewalling
2019-05-08 adjust links
2019-05-08 add image links
2019-06-05 USB armory Mk II alpha buildroot profile
2019-06-06 adjust LED path
2019-06-06 Update usbarmory mark-two devicetree
    Add support for bluetooth GPIOs (switches, reset, etc.)
2019-06-06 Fix DDR calibration values
2019-06-07 Add FUSB303 reset in U-Boot
2019-06-10 Disable over current detection for i.MX6UL
2019-06-10 i.MX6UL and i.MX6ULL device tree files update
    - enable hardware flow control on bluetooth uart
    - set plug USB port to peripheral mode
    - tidying
2019-06-12 preliminary mark-two 4.19 kernel configuration
2019-06-12 move mark-two buildroot configuration to kernel 4.19
2019-06-12 remove imx6ul pico configuration and replace it with mark-two specific one
2019-06-14 set i.MX6ULL as default DTS
2019-06-14 USB armory mark-two debug accessory
2019-06-20 comment FUSB303 i2c enable lines in u-boot patches
2019-06-20 adjust path
2019-06-20 use capabilities over tmpfs
2019-06-20 remove development ssh access
2019-06-21 enable CONFIG_IMX2_WDT to allow reboot
2019-06-24 force HAB_ENG_SW due to i.MX6ULL/i.MX6ULZ ERR010449
2019-06-27 Do not reloacate fdt initrd images
    Required to boot Linux on boards with 1GB RAM.
2019-06-27 Add U-Boot patches for boards with 1GB RAM
2019-07-01 disable CAAM on i.MX6ULL/i.MX6ULZ
2019-07-01 restore ENABLE on receptacle port
2019-07-01 bump kernel version
2019-07-01 restore USB PHY settings
2019-07-10 Fix U-Boot environment offset
    Move environment offset to 1MB to keep enough space for
    U-Boot image.
2019-07-12 first attempt at Travis CI for buildroot environment
2019-07-12 set variables as global
2019-07-12 reduce log size
2019-07-12 wait for make command
2019-07-12 remove travis integration due to time limit
2019-07-15 Add U-Boot 2017.04 patch for upstream
2019-07-22 set uSD as non-removable to work around U-Boot issue with CD
2019-07-22 specify i.MX6ULZ specific behaviour
2019-07-23 bump buildroot kernel versions
2019-07-23 Fix patch for upstream to support disabled console
    A revert of commit 80a48dd47e3bf3ede676fae5a630cb6c80de3e69
    is required to make the build successful, otherwise the following
    error is returned at the final linking stage:
    ...
    LDS u-boot.lds
    LD u-boot
2019-07-25 U-Boot advisory update
2019-07-31 bump buildroot kernel versions and apply updated mark-two u-boot patches
2019-07-31 Fix U-boot patch
    Add missing spaces in defconfig file.
2019-08-02 Fix IOMUX configuration for UART1 in U-Boot patch
2019-08-05 Fix U-Boot patch related to 1GB DDR support
2019-08-07 bump kernel versions
2019-08-07 Fix typos
2019-08-21 note orientation requirement
2019-08-26 clarify licensing
2019-09-09 Set dr_mode for plug port to peripheral
2019-09-25 Fix U-Boot mmc initialization
    Move iomux initialization for eMMC and microSD back to
    board file as the initialization via dts file appears buggy.
2019-09-30 bumped latest mxc-scc2 changeset
2019-11-07 USB armory Mk II project files + tidying
2019-11-08 add USB armory Mk II information in HAB advisory
2020-01-13 rename organization
2020-02-24 point to github page
2020-03-06 highlight default credentials
2020-03-18 add config for linux 5.4
2020-03-18 u-boot: specify boot configuration
    Mitigates CVE-2020-10648
    https://labs.f-secure.com/advisories/das-u-boot-verified-boot-bypass
2020-03-25 Fix argc argument to include USBARMORY_FIT_SIZE
    The argc argument in do_ext2load function is incorrect,
    preventing the use of USBARMORY_FIT_SIZE parameter.
2020-03-26 add serial console example for base Debian image
2020-04-02 Limit distro_bootcmd to scan a single boot device
    Regardless of the boot device, the distro_bootcmd scans both,
    microSD and eMMC, for boot scripts presence.
    A situation can arise where the U-Boot is booted from one device,
    and the Linux boot scripts are read from the other, preventing
    a complete boot from the expected device.
2020-04-02 Remove not required device tree blocks
2020-04-10 Add Mk II JTAG schematics
2020-04-24 Add DCD file for i.MX6ULZ 512MB
2020-05-04 Fix cpufreq support for imx6ulz
    https://groups.google.com/forum/#!topic/usbarmory/p4I0e22rKYw
2020-05-18 Updated DTS to use operating-points-v2 for imx6ulz
2020-06-03 remove U-Boot UMS patches, now replaced by armory-ums
2020-06-11 replace U-Boot UMS with armory-ums in buildroot installation procedure
2020-06-11 usbarmory linux: add CONFIG_SECURITY_APPARMOR
2020-06-12 u-boot: bump patches to 2020.04
2020-06-15 Fix verification boot for U-Boot 2020.04
    Remove the 'signature' devicetree block form imx6ul-usbarmory.dts
    as it goes in conflict with the one specified in usbarmory.its.
2020-06-15 Fix paths
2020-06-25 add errata note
2020-07-04 add errata comment
2020-07-24 allow crypto engine override
2020-09-17 Fix IOMUX configuration for LEDs
2020-10-20 bump u-boot patch to v2020.10
2020-12-11 update step file
2021-01-07 Add netfilter xt modules
2021-03-10 u-boot: enable TEE support
2021-03-10 u-boot: bump to v2021.01
2021-03-10 kernel: add linux config 5.10
    - add TEE support
    - align dts file for 5.10 kernel version
2021-03-10 align imx6ul devicetree to kernel 5.10
2021-03-15 add link to habtool
2021-05-07 linux: update config for 5.10.34
2021-05-14 buildroot update
2021-06-14 add USB armory Mk II rev. γ STEP file
2021-07-22 u-boot: bump to v2021.07
2021-07-30 Add HS200 MMC mode
    On gamma use HS200 mode on eMMC:
    mmc1: new HS200 MMC card at address 0001
    On beta revisions will fallback to default DDR MMC mode:
    mmc1: mmc_select_hs200 failed, error -74
    mmc1: new DDR MMC card at address 0001
2021-08-04 Fix debug accessory documentation
2021-09-20 links update
2021-09-30 buildroot profiles are no longer mantained
2021-11-12 Enable cpu idle
2021-11-12 Align U-Boot config to v2021.10
2021-11-22 Compile RNGB driver as module
2021-11-23 Revert "Compile RNGB driver as module"
    This reverts commit 99c710d7c7e7e14902887094457c5fd03dc011d2.
2021-11-23 Add dts node for optee driver
2022-03-09 Add config for linux 5.15
2022-03-10 mark-one: add config for linux 5.15
2022-03-23 Add kernel defconfig for mark-one and mark-two
2022-03-28 Align to U-Boot v2022.01
2022-03-28 Fix verified boot
    Based on:
    https://github.com/sergioag/usbarmory_u-boot/commit/a325c085feacb1468811dcc2a8a9d5b4fde8744d
2022-03-31 fix mark-one USB
2022-05-09 Align to U-Boot v2022.04
2022-06-28 bump u-boot patch to v2022.04
2022-07-19 Fix boot in non-secure mode
2022-07-20 Align to U-Boot v2022.07
2022-11-14 Align to U-Boot 2022.10
2022-11-23 imc6ul: use 1GB ram
2023-01-12 linux: enable binfmt_misc
2023-03-15 Align to U-Boot 2023.01
2023-04-14 add dts
2023-05-02 Add imx6ulz 1G non secure devicetree
2023-06-20 Align to U-Boot 2023.04
2023-07-20 Align to U-Boot v2023.07
2023-07-20 Fix for mark-one u-boot
2023-10-02 add PoE silkscreen
2023-11-10 Fix comments
2024-01-26 bump u-boot config to 2024.01
2024-04-04 bump u-boot config to 2024.04
2024-04-19 add USB armory Mk II LAN configs
2024-07-02 bump u-boot config to 2024.07
2024-10-29 bump u-boot patch to 2024.10
2025-04-10 bump u-boot- patch to 2025.04
2025-04-28 update emails
2025-08-28 license/copyright update
